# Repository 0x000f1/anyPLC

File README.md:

<div align="center">

# anyPLC

**Compact 50 × 50 mm, 4-Layer ESP32-C3 Industrial PWM & Telemetry Controller for ESPHome**

<br>

*Raytraced 3D render of the **anyPLC Rev 1.1** front side (50 × 50 mm, 4-layer PCB)*

</div>

---

## Overview

**anyPLC** is a compact, industrial-grade, Wi-Fi/BLE smart controller built around the **ESP32-C3-MINI-1** module and designed for seamless integration with **ESPHome** and **Home Assistant**.

It is engineered for reliable, closed-loop control of **12–24 V DC loads** in tight enclosures, including:
* High-power 12 V / 24 V PWM cooling fans with real-time RPM (tachometer) feedback
* DC water/dosing pumps, solenoids, valves, and inductive actuators (protected by onboard freewheeling diodes)
* High-current DC LED strips or low-voltage resistive heaters
* Autonomous monitoring setups requiring real-time bus voltage/current telemetry and hardware watchdog recovery

<details>
<summary><b>View Front & Back PCB Renders</b></summary>
<br>

| Front Side (`F.Cu`) | Back Side (`B.Cu`) |
| :---: | :---: |
|  |  |

</details>

---

## Hardware Architecture & Specifications

| Subsystem | Components & Specifications |
| :--- | :--- |
| **MCU & Radio** | **ESP32-C3-MINI-1** (`U4`) — 32-bit RISC-V, Wi-Fi 4 + BLE 5, integrated 40 MHz crystal & flash, unobstructed edge antenna keepout |
| **Power Input** | **12–24 V DC** (`J1`), **8 A** input fuse (`F1`), P-channel MOSFET reverse-polarity protection (`Q1`) with ~15 V V<sub>GS</sub> Zener clamp (`DZ1`, `R2`), and **SMBJ26A** TVS surge suppressor (`D1`) |
| **Power Rails** | Dual independent buck stages:<br>• **+5 V Rail (`U2`):** `TPS54360B` (~4.98 V, ~485 kHz, `B560C` catch diode `D_BUCK1`, `L1`)<br>• **+3.3 V Rail (`U3`):** `SY8089` (~3.33 V, fed from +5 V, `L2`) |
| **Power Telemetry** | **INA226** (`U1`) bus voltage & current monitor across a **10 mΩ (2512)** shunt (`R1`) with Kelvin sensing (`R3`/`R4` 10 Ω + `C3`), I2C address **`0x44`**, open-drain `INA_ALERT` pull-up (`R_INA1` 10 kΩ) |
| **Dual PWM Outputs** | 2× low-side N-channel PWM MOSFET stages (`Q2`, `Q3`) driven at +5 V by a dedicated dual gate driver (`U_DRV1`, 10 Ω gate resistors `R13`/`R18`, 10 kΩ pulldowns `R14`/`R19`), **B560C** (60 V / 5 A) freewheeling diodes (`D3`, `D5`), and per-channel active LEDs (`D4`, `D6`) |
| **Tachometer Inputs** | 2× optocoupled open-collector/open-drain tachometer inputs (`U7`, `U8` — `TLP293`), reverse-blocking diodes (`D_TCH1`/`D_TCH2` `1N4148W`), ~1.3 mA LED drive from +5 V, 10 kΩ output pull-ups (`R15`/`R20`) to +3.3 V |
| **Expansion Ports** | Dedicated **I2C** (`J2`, onboard 4.7 kΩ pull-ups `R9`/`R10`) and **UART** (`J3`, 100 Ω series resistors `R11`/`R12`), protected by **SRV05-4** ESD diode array (`U6`) |
| **Hardware Watchdog** | External **STWD100** watchdog timer (`U5`) tied to MCU `EN`, with hardware enable/disable solder jumper (`JP1`, 4.7 kΩ pull-up `R_WD_EN1`) |
| **Status & Debug** | Addressable RGB status LED (`D_RGB1`, WS2812-type) and 2×4 pogo-pad programming/debug interface (`J6`) exposing UART, native USB, `EN`, and `BOOT` |
| **PCB Form Factor** | **50 × 50 mm**, 4-layer stackup (`F.Cu` / `GND` / `Power` / `B.Cu`), 1.6 mm FR-4, teardrops, and dual-sided fiducials for automated PCBA |

---

## Connector Pinouts

### `J1` — Power Input (12–24 V DC)
| Pin | Net | Function |
| :---: | :--- | :--- |
| 1 | `VIN+` | 12–24 V DC input (via `F1` 8 A fuse & `Q1` reverse-polarity MOSFET) |
| 2 | `GND` | System ground |

### `J4` (CH1) & `J5` (CH2) — PWM Output & Tachometer Terminals
| Pin | Net | Function |
| :---: | :--- | :--- |
| 1 | `+V_IN_MAIN` | Protected supply positive (12–24 V DC, load `+`) |
| 2 | `PWM OUT` | Low-side MOSFET Drain (load `-`, flyback diode to Pin 1) |
| 3 | `GND` | System ground |
| 4 | `+5V` | Regulated +5 V auxiliary supply (e.g., for fan electronics / sensors) |
| 5 | `TACHO` | Optocoupled tachometer input (active-low open-collector/open-drain pull-down) |

### `J2` (I2C) & `J3` (UART) — Expansion Ports (**3.3 V Logic Only**)
| Pin | `J2` (I2C) | `J3` (UART) |
| :---: | :--- | :--- |
| 1 | `GND` | `GND` |
| 2 | `+3.3V` | `+3.3V` |
| 3 | `I2C_SDA` (4.7 kΩ pull-up to 3.3 V) | `UART_TX` (via 100 Ω `R11`, ESD protected) |
| 4 | `I2C_SCL` (4.7 kΩ pull-up to 3.3 V) | `UART_RX` (via 100 Ω `R12`, ESD protected) |

### `J6` — Programming & Debug Pogo-Pad (2×4, Bottom Side)
| Pin | Function | Pin | Function |
| :---: | :--- | :---: | :--- |
| 1 | `+3.3V` | 5 | `EN` (Reset) |
| 2 | `GND` | 6 | `BOOT` (`GPIO9`) |
| 3 | `UART_TX` (ESP TXD) | 7 | `USB_D+` |
| 4 | `UART_RX` (ESP RXD) | 8 | `USB_D-` |

### `JP1` — Watchdog Enable Jumper (Bottom Side)
| State | Watchdog (`STWD100`) Behavior |
| :--- | :--- |
| **OPEN** *(default)* | **Disabled** (`R_WD_EN1` pulls enable high). Required during firmware flashing and bench debugging. |
| **CLOSED** *(bridged)* | **Enabled**. Firmware must periodically toggle `WDI` to prevent automatic MCU resets. |

---

## Important Notes, Precautions & Known Limitations

Read these before assembly, flashing, or field deployment:

1. **Keep `JP1` OPEN when flashing:** With `JP1` bridged, the external `STWD100` watchdog receives no `WDI` pulses while the ESP32-C3 is in ROM bootloader mode and will continuously reset the chip. Bridge `JP1` only after flashing firmware that actively feeds `WDI`.
2. **Disconnect `J3` during UART flashing:** `J6` (pogo-pad) and `J3` (UART expansion port) share the same `UART_TX` / `UART_RX` lines (coupled through 100 Ω `R11`/`R12`). Unplug any peripheral on `J3` while flashing through `J6` to avoid bus contention.
3. **`J2` and `J3` are strictly 3.3 V logic:** The `SRV05-4` ESD array (`U6`) clamps I/O pins directly to `+3.3V`. Connecting 5 V I2C or UART logic will forward-bias the clamp diodes above ~4 V and back-feed the 3.3 V rail and ESP32-C3 pins.
4. **INA226 I2C address is `0x44` (not `0x40`):** `U1` has `A1` strapped to `+3.3V` and `A0` to `GND`. Configure `address: 0x44` in ESPHome. Note that `0x44` is also the default I2C address of **SHT3x** temperature/humidity sensors — if connecting an SHT3x to `J2`, strap the sensor's address pin to `0x45` to avoid a bus collision.
5. **No per-port PTC fuses on auxiliary rails:** `+3.3V` (`J2.2`, `J3.2`) and `+5V` (`J4.4`, `J5.4`) connect directly to the internal buck rails. Shorting an external sensor cable will brown out the MCU (`+3.3V`) or put `U2` (`+5V` TPS54360B) into hiccup mode, collapsing both rails.
6. **No external ESD diodes on `J6` USB lines:** `USB_D+` and `USB_D-` run directly from `J6` to `U4`. The pogo-pad header is intended for ESD-safe bench/factory programming rather than exposed field hot-plugging.
7. **24 V hot-plug transient margin:** `SMBJ26A` (`D1`) has a peak clamping voltage up to 42.1 V under rated surge current, while the `INA226` absolute maximum rating is 40 V. Operate within 12–24 V DC nominal and avoid severe unbuffered inductive hot-plug spikes.
8. **First-board bring-up verification:** On initial power-up at 24 V, verify the `+5V` (~4.98 V) and `+3.3V` (~3.33 V) rails before soldering `JP1`, and scope-check the `U2` switch node (`SW`) under load to confirm overshoot stays safely within the `B560C` 60 V rating.

---

## Bring-Up & Flashing Quick Checklist

1. Inspect the assembled board for solder bridges, confirm `JP1` is **open**, and ensure nothing is connected to `J3`.
2. Power the board from a current-limited bench supply (12–24 V DC, ~150 mA limit initially) and verify `+5V` and `+3.3V` rails.
3. Connect your USB/UART programmer to `J6` and flash your ESPHome firmware (include `address: 0x44` in the `ina226:` block).
4. Verify I2C bus discovery (`0x44` for INA226), PWM channel switching (`D4`/`D6`), and tachometer pulse counting.
5. Once your firmware reliably toggles the `WDI` pin, bridge `JP1` to activate the hardware watchdog for deployment.

---

## PCB Manufacturing & DFM

* **Dimensions:** 50.0 × 50.0 mm
* **Layers:** 4 layers (`F.Cu` Signal / `In1.Cu` Solid GND / `In2.Cu` Split Power `+V_IN_MAIN`, `+5V`, `+3.3V` / `B.Cu` Signal)
* **Design Rules:** Verified against JLCPCB 4-layer standard capabilities (min clearance 0.125 mm, min track 0.15 mm, standard vias 0.50 mm / 0.30 mm drill, `U2` thermal pad vias 0.20 mm drill)
* **DFM Features:** Teardrops enabled on pads and vias, 3+3 asymmetric fiducial markers (`F.Cu` and `B.Cu`), tented vias, `JLCJLCJLCJLC` order-number placeholder on `B.Silkscreen`
* **Assembly Note:** If hand-soldering with paste and hot air, request tented/plugged vias or watch solder wicking on the `U2` thermal vias and the central hole of `U4` pad 49.

---

## Repository Structure

```text
anyPLC/
├── anyPLC.kicad_pro          # KiCad 10 project file
├── anyPLC.kicad_sch          # Multi-sheet schematic
├── anyPLC.kicad_pcb          # 4-layer PCB layout
├── docs/
│   └── images/               # Raytraced 3D renders & documentation assets
├── production/               # Gerber, Drill, BOM, CPL, and iBOM outputs
└── README.md
```

---

## Hardware Revisions

* **Rev 1.1** *(Current)* — Initial 4-layer production candidate (`DRC: 0 errors, 0 unconnected`, netlist-audited). Includes teardrops, dual-sided fiducials, repository QR code, ESD markings, and full bottom-side pinout silkscreen.

---

## License

* **Hardware** (schematics, PCB layout, manufacturing files): Licensed under the **CERN Open Hardware Licence Version 2 - Strongly Reciprocal (CERN-OHL-S v2)**.
* **Software & Documentation** (ESPHome configs, scripts, docs): Licensed under the **MIT License**.

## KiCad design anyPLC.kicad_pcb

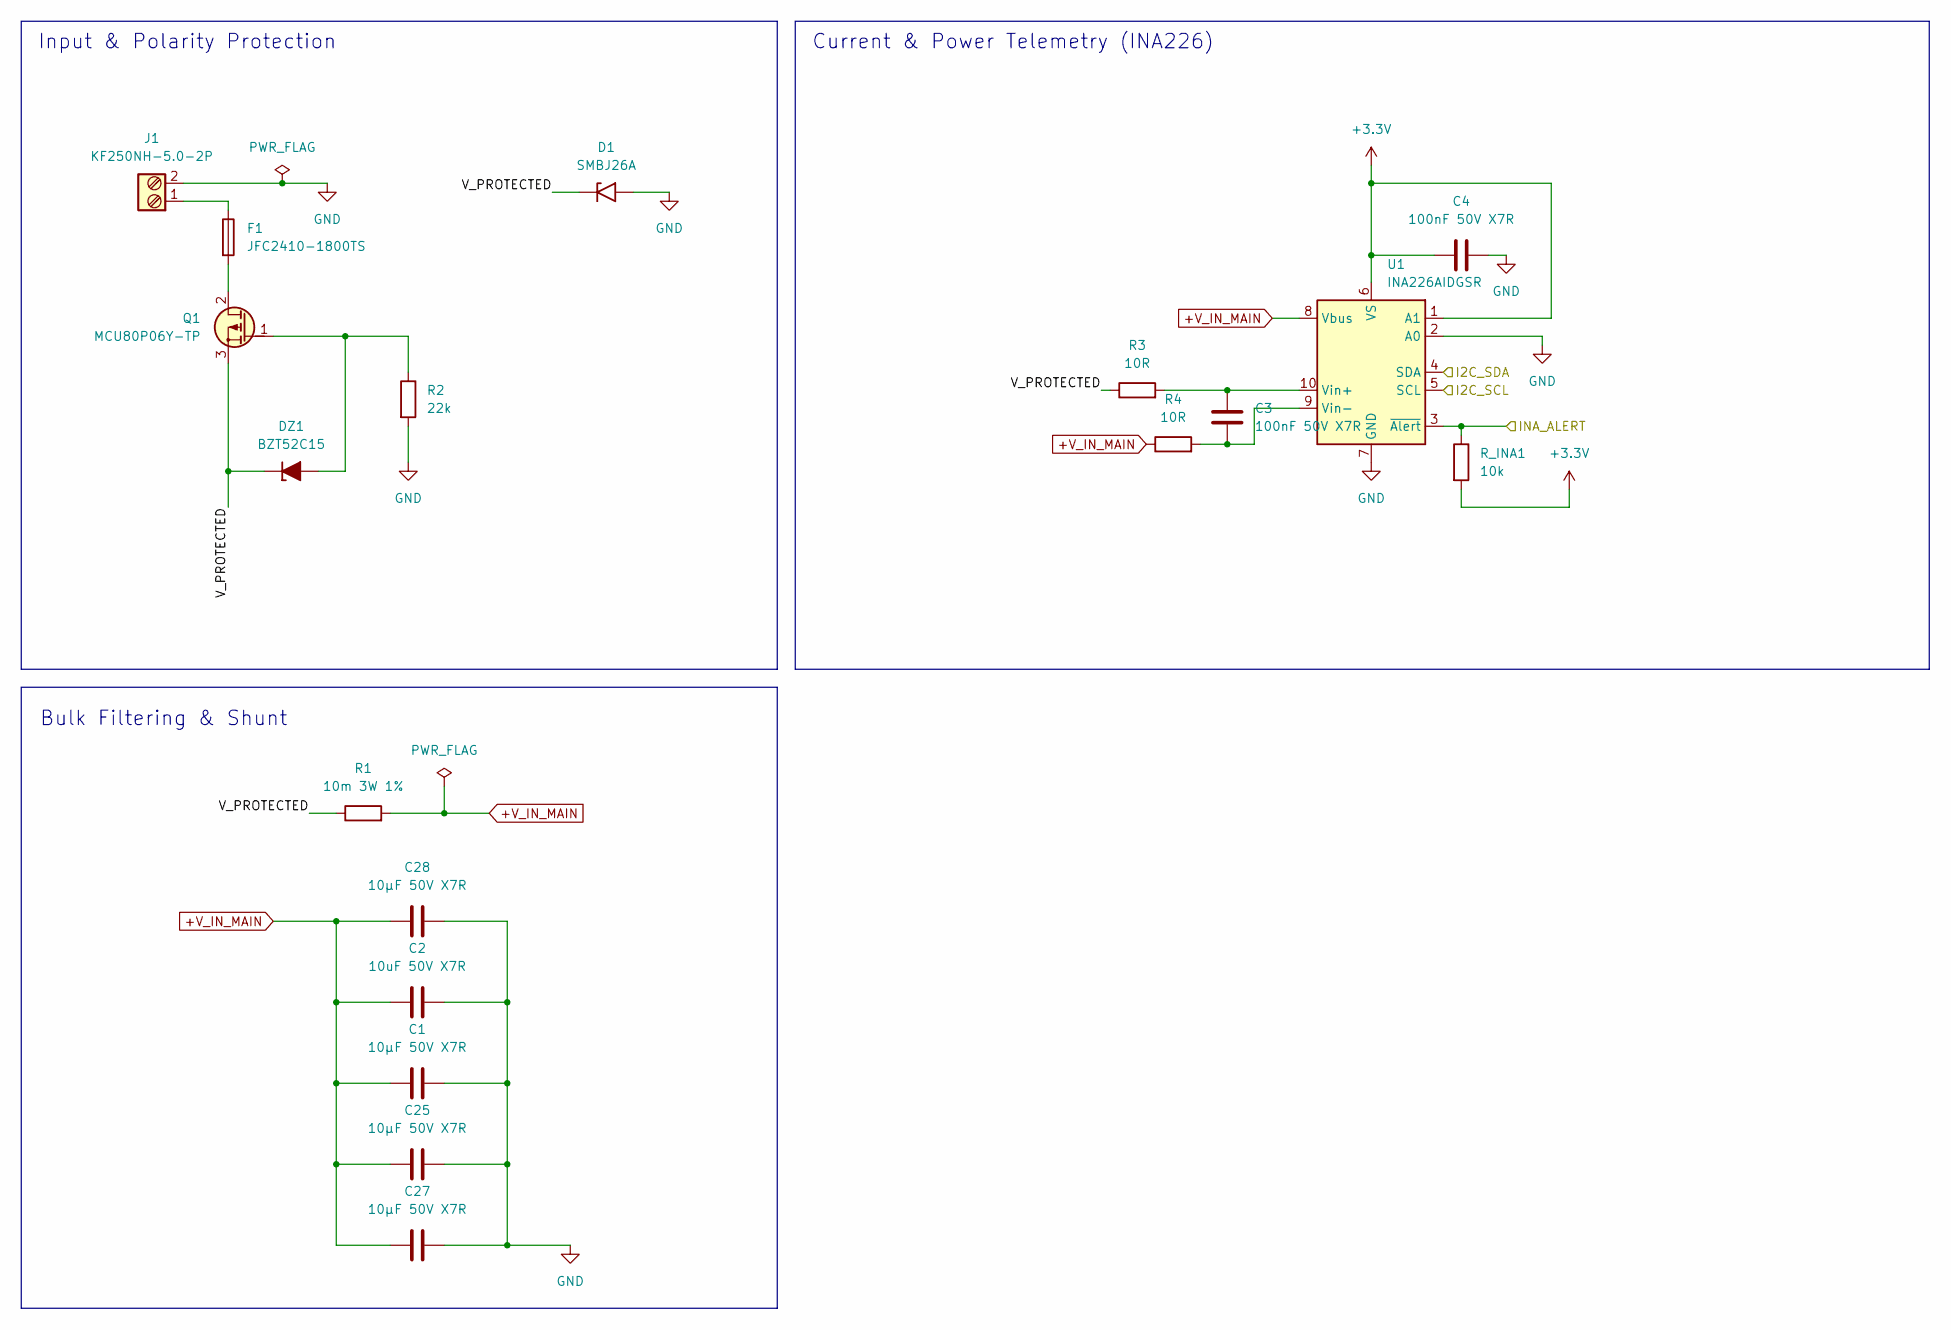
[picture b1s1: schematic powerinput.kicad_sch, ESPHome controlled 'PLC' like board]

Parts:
C1, C25, C27, C28: 10µF 50V X7R; C_1206_3216Metric_Pad1.33x1.80mm_HandSolder
C2: 10uF 50V X7R; C_1206_3216Metric_Pad1.33x1.80mm_HandSolder
C3, C4: 100nF 50V X7R; C_0603_1608Metric_Pad1.08x0.95mm_HandSolder
D1: SMBJ26A; D_SMB_Handsoldering
DZ1: BZT52C15; D_SOD-123
F1: JFC2410-1800TS; F2410
J1: KF250NH-5.0-2P; CONN-TH_KF250NH-5.0-2P
Q1: MCU80P06Y-TP; TO-252-2
R1: 10m 3W 1%; R_2512_6332Metric_Pad1.40x3.35mm_HandSolder
R2: 22k; R_0603_1608Metric_Pad0.98x0.95mm_HandSolder
R3, R4: 10R; R_0603_1608Metric_Pad0.98x0.95mm_HandSolder
R_INA1: 10k; R_0603_1608Metric_Pad0.98x0.95mm_HandSolder
U1: INA226AIDGSR; TSSOP-10_3x3mm_P0.5mm

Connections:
+3.3V: C4.1, R_INA1.2, U1.1 (A1), U1.6 (VS); also elsewhere on the board
+V_IN_MAIN: C1.1, C2.2, C25.1, C27.1, C28.1, R1.2, R4.1, U1.8 (Vbus); also elsewhere on the board
/MCU Core/I2C_SCL: U1.5 (SCL); also elsewhere on the board
/MCU Core/I2C_SDA: U1.4 (SDA); also elsewhere on the board
/MCU Core/INA_ALERT: R_INA1.1, U1.3 (~Alert); also elsewhere on the board
/Power Input/V_PROTECTED: D1.1 (A1), DZ1.1 (K), Q1.3 (S), R1.1, R3.1
GND: C1.2, C2.1, C4.2, C25.2, C27.2, C28.2, D1.2 (A2), J1.2, R2.2, U1.2 (A0), U1.7 (GND); also elsewhere on the board
unnamed: DZ1.2 (A), Q1.1 (G), R2.1
unnamed: F1.1, J1.1
unnamed: F1.2, Q1.2 (D)
unnamed: C3.1, R3.2, U1.10 (Vin+)
unnamed: C3.2, R4.2, U1.9 (Vin-)

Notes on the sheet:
Input & Polarity Protection
Bulk Filtering & Shunt
Current & Power Telemetry (INA226)

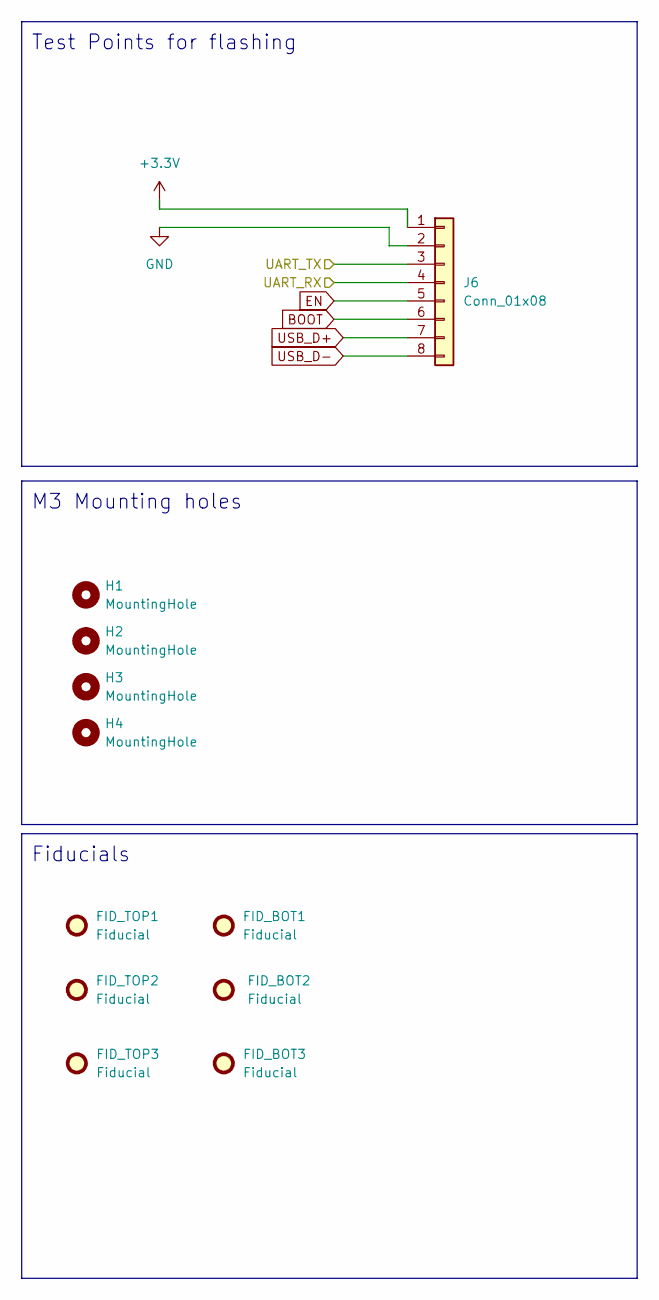
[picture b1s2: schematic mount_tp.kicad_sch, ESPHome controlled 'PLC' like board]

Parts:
FID_BOT1, FID_BOT2, FID_BOT3: Fiducial; Fiducial_1mm_Mask2mm
FID_TOP1, FID_TOP2, FID_TOP3: Fiducial; Fiducial_1mm_Mask2mm
H1, H2, H3, H4: MountingHole; MountingHole_3.2mm_M3_ISO14580
J6: Conn_01x08; TestPoint_2x04_P2.54mm_D1.6mm_SMD

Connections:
+3.3V: J6.1; also elsewhere on the board
/MCU Core/UART_RX: J6.4; also elsewhere on the board
/MCU Core/UART_TX: J6.3; also elsewhere on the board
BOOT: J6.6; also elsewhere on the board
EN: J6.5; also elsewhere on the board
GND: J6.2; also elsewhere on the board
USB_D+: J6.7; also elsewhere on the board
USB_D-: J6.8; also elsewhere on the board

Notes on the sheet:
M3 Mounting holes
Test Points for flashing
Fiducials

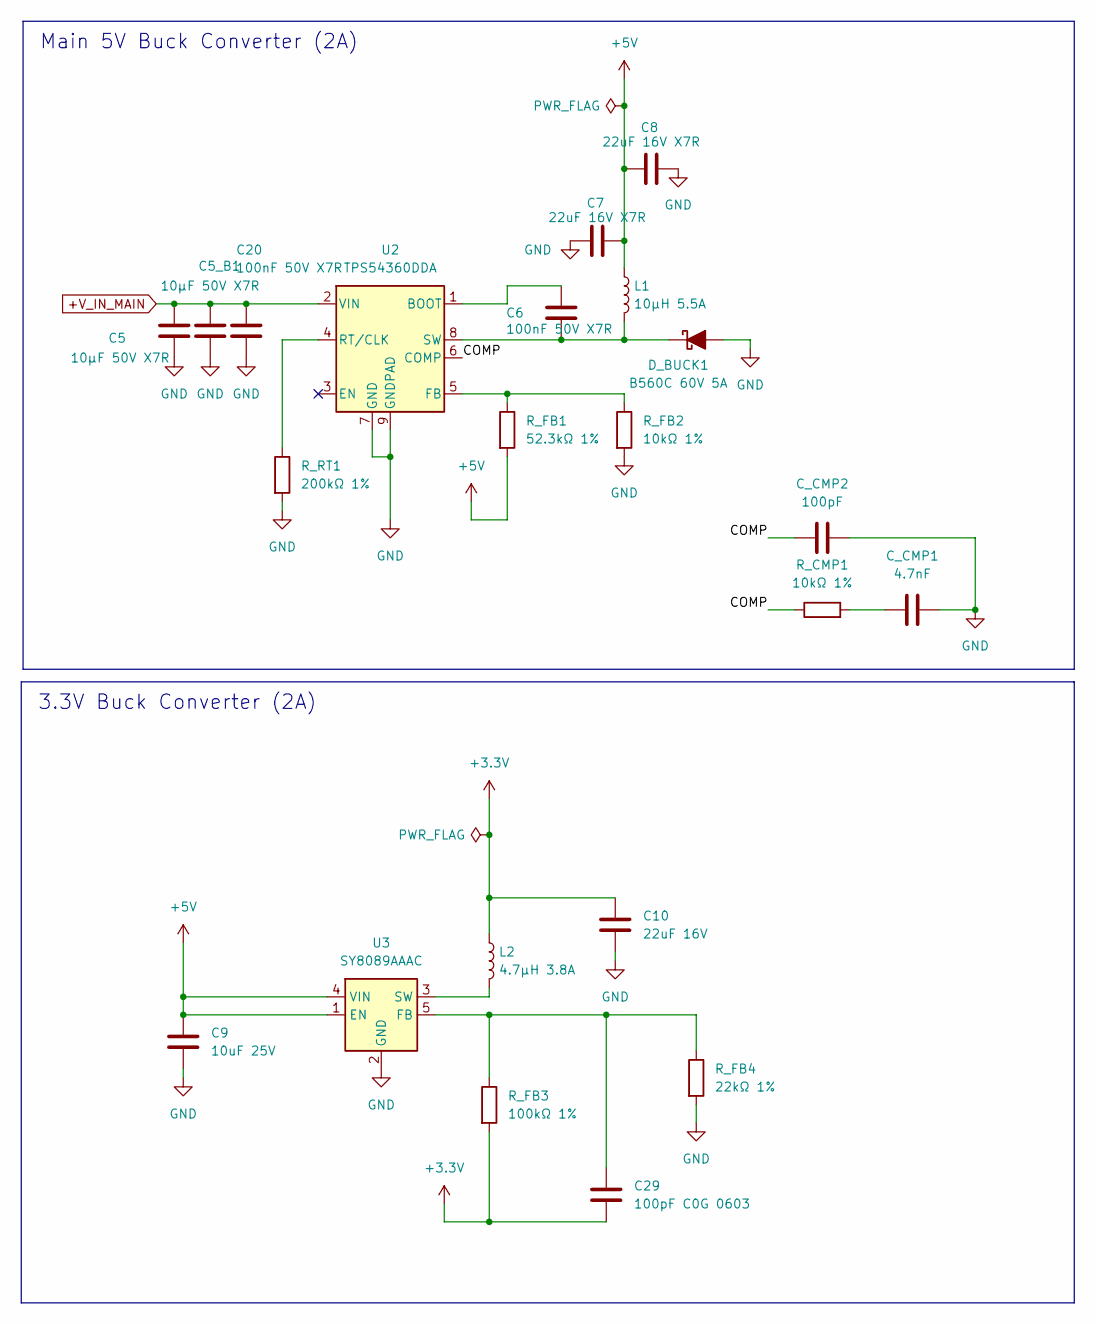
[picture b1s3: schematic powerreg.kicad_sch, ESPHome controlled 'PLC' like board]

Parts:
C5, C5_B1: 10µF 50V X7R; C_1206_3216Metric_Pad1.33x1.80mm_HandSolder
C6, C20: 100nF 50V X7R; C_0603_1608Metric_Pad1.08x0.95mm_HandSolder
C7, C8: 22uF 16V X7R; C_1206_3216Metric_Pad1.33x1.80mm_HandSolder
C9: 10uF 25V; C_0805_2012Metric_Pad1.18x1.45mm_HandSolder
C10: 22uF 16V; C_1206_3216Metric_Pad1.33x1.80mm_HandSolder
C29: 100pF C0G 0603; C_0603_1608Metric_Pad1.08x0.95mm_HandSolder
C_CMP1: 4.7nF; C_0603_1608Metric_Pad1.08x0.95mm_HandSolder
C_CMP2: 100pF; C_0603_1608Metric_Pad1.08x0.95mm_HandSolder
D_BUCK1: B560C 60V 5A; D_SMC_Handsoldering
L1: 10µH 5.5A; IND-SMD_L7.3-W6.6
L2: 4.7µH 3.8A; IND-SMD_L5.0-W5.0_FNR50XXS
R_CMP1: 10kΩ 1%; R_0603_1608Metric_Pad0.98x0.95mm_HandSolder
R_FB1: 52.3kΩ 1%; R_0603_1608Metric_Pad0.98x0.95mm_HandSolder
R_FB2: 10kΩ 1%; R_0603_1608Metric_Pad0.98x0.95mm_HandSolder
R_FB3: 100kΩ 1%; R_0603_1608Metric_Pad0.98x0.95mm_HandSolder
R_FB4: 22kΩ 1%; R_0603_1608Metric_Pad0.98x0.95mm_HandSolder
R_RT1: 200kΩ 1%; R_0603_1608Metric_Pad0.98x0.95mm_HandSolder
U2: TPS54360DDA; SOIC-8-1EP_3.9x4.9mm_P1.27mm_EP2.41x3.3mm
U3: SY8089AAAC; SOT-23-5_HandSoldering

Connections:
+3.3V: C10.1, C29.2, L2.1, R_FB3.2; also elsewhere on the board
+5V: C7.1, C8.1, C9.1, L1.1, R_FB1.2, U3.1 (EN), U3.4 (VIN); also elsewhere on the board
+V_IN_MAIN: C5.2, C5_B1.2, C20.2, U2.2 (VIN); also elsewhere on the board
/Power Regulators/COMP: C_CMP2.1, R_CMP1.1, U2.6 (COMP)
GND: C5.1, C5_B1.1, C7.2, C8.2, C9.2, C10.2, C20.1, C_CMP1.2, C_CMP2.2, D_BUCK1.2 (A), R_FB2.2, R_FB4.2, R_RT1.2, U2.7 (GND), U2.9 (GNDPAD), U3.2 (GND); also elsewhere on the board
unnamed: C_CMP1.1, R_CMP1.2
unnamed: C6.1, D_BUCK1.1 (K), L1.2, U2.8 (SW)
unnamed: C6.2, U2.1 (BOOT)
unnamed: R_FB1.1, R_FB2.1, U2.5 (FB)
unnamed: R_RT1.1, U2.4 (RT/CLK)
unnamed: C29.1, R_FB3.1, R_FB4.1, U3.5 (FB)
unnamed: L2.2, U3.3 (SW)

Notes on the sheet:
Main 5V Buck Converter (2A)
3.3V Buck Converter (2A)

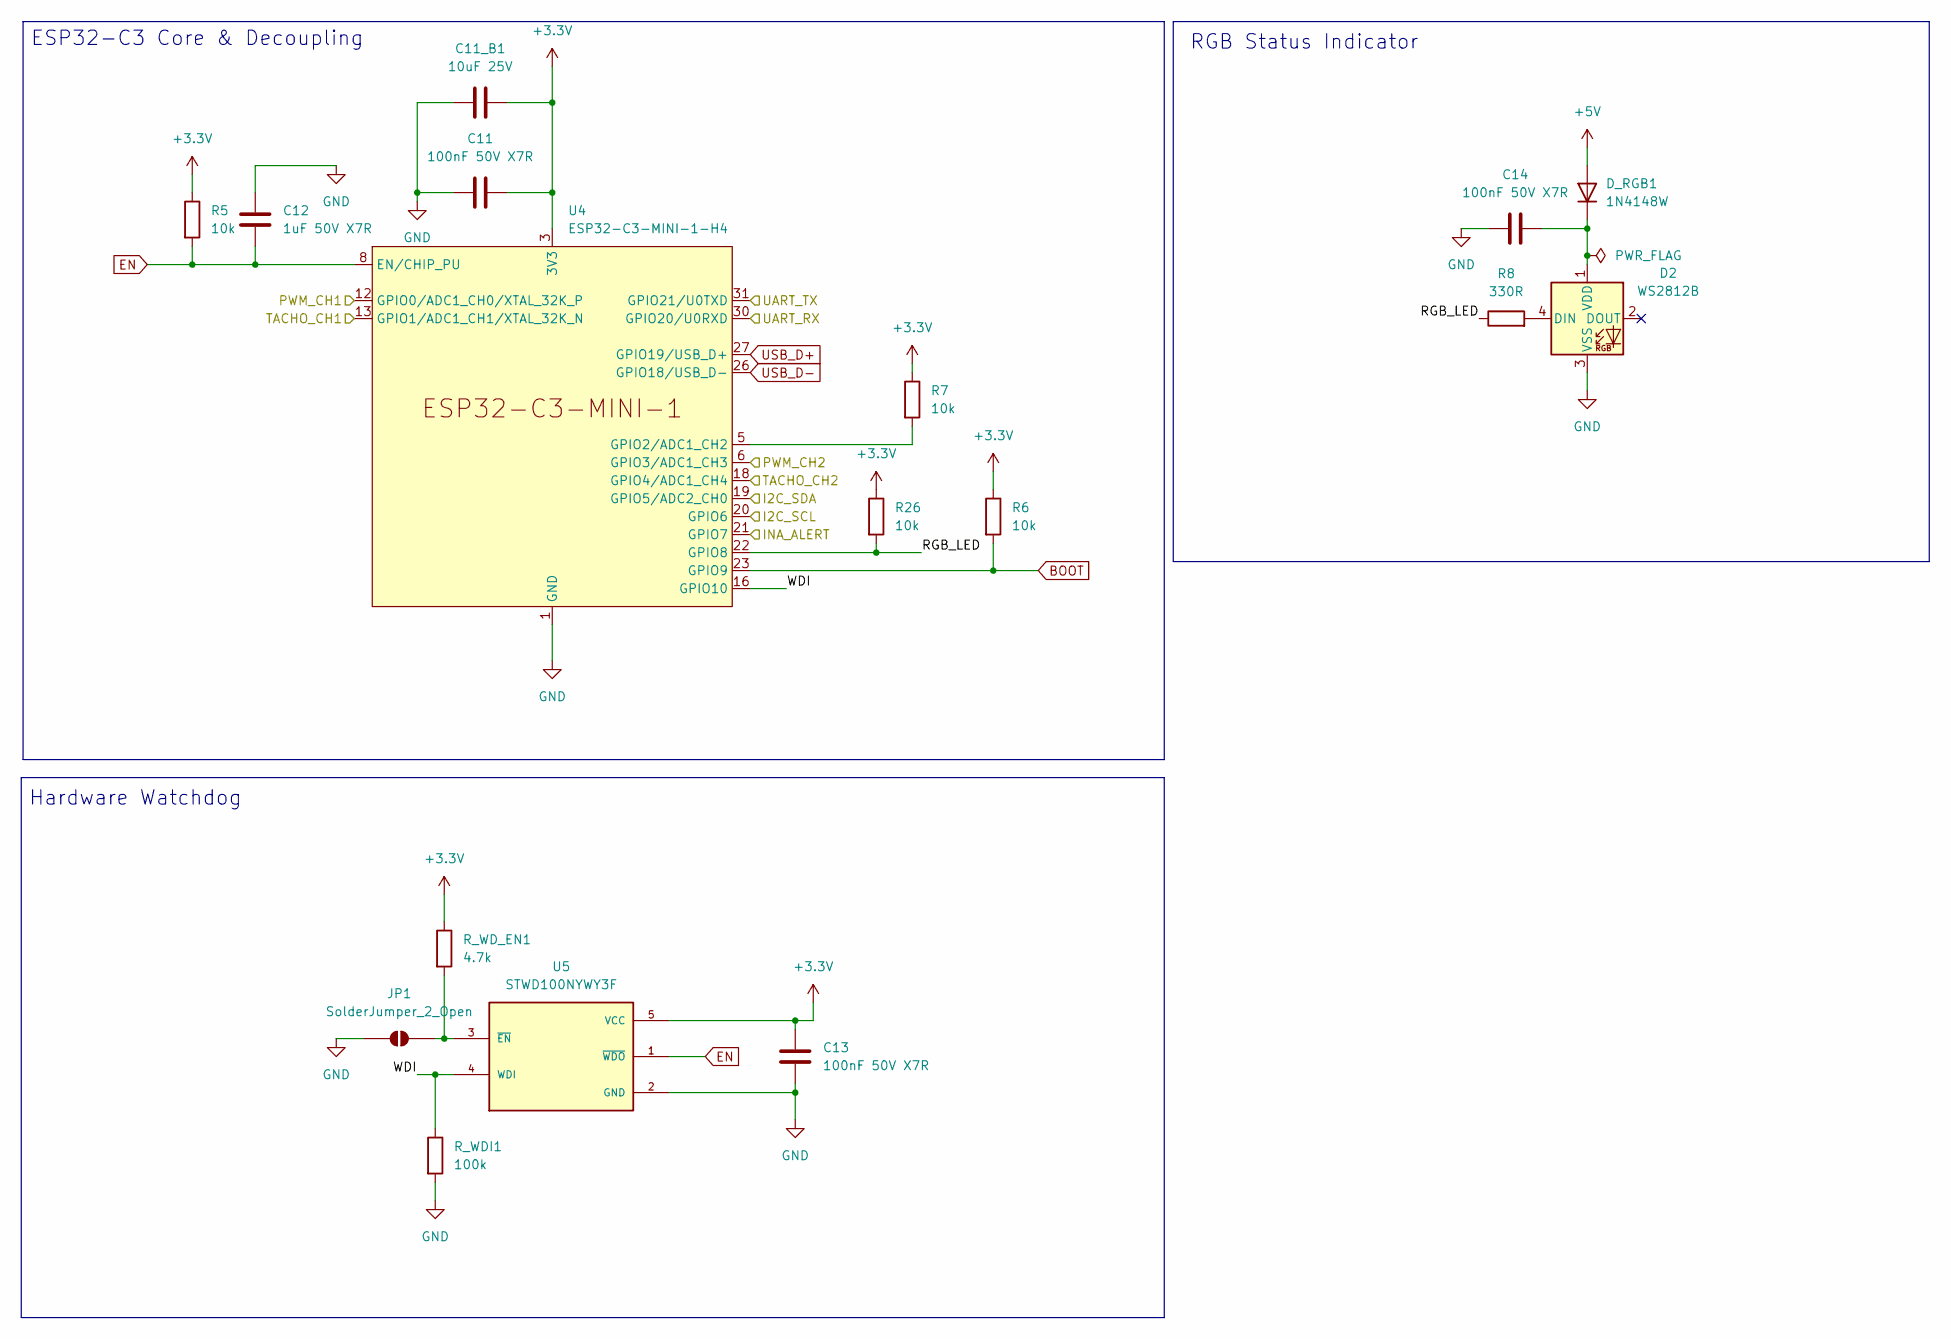
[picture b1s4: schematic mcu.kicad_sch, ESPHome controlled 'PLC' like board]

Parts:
C11, C13, C14: 100nF 50V X7R; C_0603_1608Metric_Pad1.08x0.95mm_HandSolder
C11_B1: 10uF 25V; C_0805_2012Metric_Pad1.18x1.45mm_HandSolder
C12: 1uF 50V X7R; C_0603_1608Metric_Pad1.08x0.95mm_HandSolder
D2: WS2812B; LED_WS2812B_PLCC4_5.0x5.0mm_P3.2mm
D_RGB1: 1N4148W; D_SOD-123
JP1: SolderJumper_2_Open; SolderJumper-2_P1.3mm_Open_RoundedPad1.0x1.5mm
R5, R6, R7, R26: 10k; R_0603_1608Metric_Pad0.98x0.95mm_HandSolder
R8: 330R; R_0603_1608Metric_Pad0.98x0.95mm_HandSolder
R_WDI1: 100k; R_0603_1608Metric_Pad0.98x0.95mm_HandSolder
R_WD_EN1: 4.7k; R_0603_1608Metric_Pad0.98x0.95mm_HandSolder
U4: ESP32-C3-MINI-1-H4; ESP32-C3-MINI-1
U5: STWD100NYWY3F; SOT-23-5_HandSoldering; MPN STWD100NYWY3F

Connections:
+3.3V: C11.2, C11_B1.2, C13.1, R5.1, R6.1, R7.1, R26.1, R_WD_EN1.1, U4.3 (3V3), U5.5 (VCC); also elsewhere on the board
+5V: D_RGB1.2 (A); also elsewhere on the board
/MCU Core/I2C_SCL: U4.20 (GPIO6); also elsewhere on the board
/MCU Core/I2C_SDA: U4.19 (GPIO5/ADC2_CH0); also elsewhere on the board
/MCU Core/INA_ALERT: U4.21 (GPIO7); also elsewhere on the board
/MCU Core/PWM_CH1: U4.12 (GPIO0/ADC1_CH0/XTAL_32K_P); also elsewhere on the board
/MCU Core/PWM_CH2: U4.6 (GPIO3/ADC1_CH3); also elsewhere on the board
/MCU Core/RGB_LED: R8.1, R26.2, U4.22 (GPIO8)
/MCU Core/TACHO_CH1: U4.13 (GPIO1/ADC1_CH1/XTAL_32K_N); also elsewhere on the board
/MCU Core/TACHO_CH2: U4.18 (GPIO4/ADC1_CH4); also elsewhere on the board
/MCU Core/UART_RX: U4.30 (GPIO20/U0RXD); also elsewhere on the board
/MCU Core/UART_TX: U4.31 (GPIO21/U0TXD); also elsewhere on the board
/MCU Core/WDI: R_WDI1.1, U4.16 (GPIO10), U5.4 (WDI)
BOOT: R6.2, U4.23 (GPIO9); also elsewhere on the board
EN: C12.2, R5.2, U4.8 (EN/CHIP_PU), U5.1 (~WDO); also elsewhere on the board
GND: C11.1, C11_B1.1, C12.1, C13.2, C14.1, D2.3 (VSS), JP1.1 (A), R_WDI1.2, U4.1 (GND), U4.2 (GND), U4.11 (GND), U4.14 (GND), U4.36 (GND), U4.37 (GND), U4.38 (GND), U4.39 (GND), U4.40 (GND), U4.41 (GND), U4.42 (GND), U4.43 (GND), U4.44 (GND), U4.45 (GND), U4.46 (GND), U4.47 (GND), U4.48 (GND), U4.49 (GND), U4.50 (GND), U4.51 (GND), U4.52 (GND), U4.53 (GND), U5.2 (GND); also elsewhere on the board
unnamed: D2.4 (DIN), R8.2
unnamed: C14.2, D2.1 (VDD), D_RGB1.1 (K)
unnamed: JP1.2 (B), R_WD_EN1.2, U5.3 (~EN)
unnamed: R7.2, U4.5 (GPIO2/ADC1_CH2)
USB_D+: U4.27 (GPIO19/USB_D+); also elsewhere on the board
USB_D-: U4.26 (GPIO18/USB_D-); also elsewhere on the board

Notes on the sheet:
Hardware Watchdog
RGB Status Indicator
ESP32-C3 Core & Decoupling

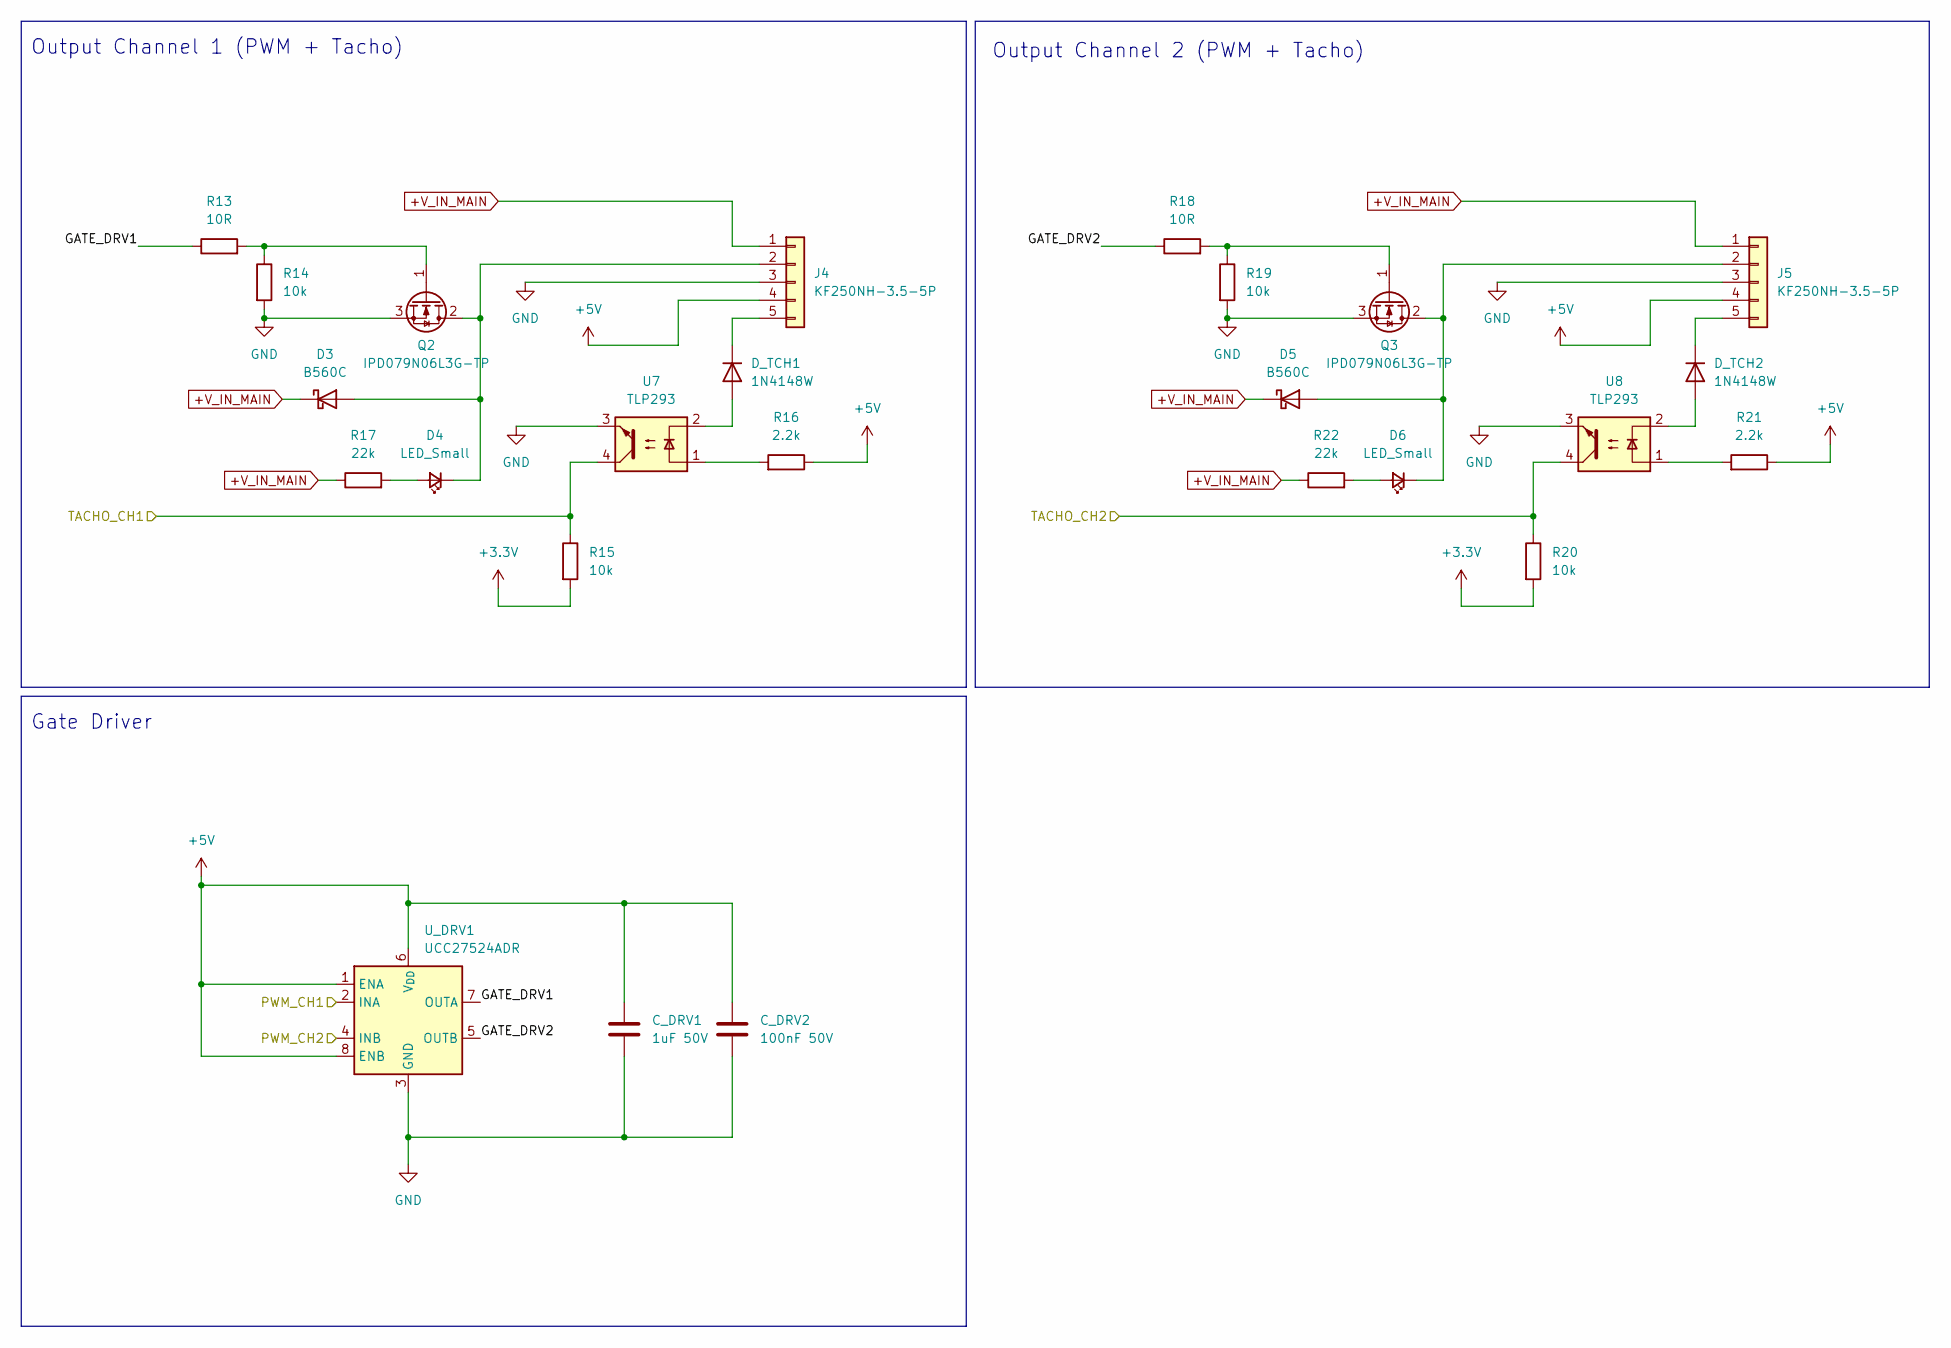
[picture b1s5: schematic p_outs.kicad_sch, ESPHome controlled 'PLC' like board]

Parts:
C_DRV1: 1uF 50V; C_0603_1608Metric_Pad1.08x0.95mm_HandSolder
C_DRV2: 100nF 50V; C_0603_1608Metric_Pad1.08x0.95mm_HandSolder
D3, D5: B560C; D_SMC_Handsoldering
D4, D6: LED_Small; LED_0603_1608Metric_Pad1.05x0.95mm_HandSolder
D_TCH1, D_TCH2: 1N4148W; D_SOD-123
J4, J5: KF250NH-3.5-5P; CONN-TH_KF250NH-3.5-5P
Q2, Q3: IPD079N06L3G-TP; TO-252-2
R13, R18: 10R; R_0603_1608Metric_Pad0.98x0.95mm_HandSolder
R14, R15, R19, R20: 10k; R_0603_1608Metric_Pad0.98x0.95mm_HandSolder
R16, R21: 2.2k; R_0603_1608Metric_Pad0.98x0.95mm_HandSolder
R17, R22: 22k; R_0603_1608Metric_Pad0.98x0.95mm_HandSolder
U7, U8: TLP293; SOP-4_4.4x2.6mm_P1.27mm
U_DRV1: UCC27524ADR; SOIC-8_3.9x4.9mm_P1.27mm

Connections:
+3.3V: R15.2, R20.2; also elsewhere on the board
+5V: C_DRV1.1, C_DRV2.1, J4.4, J5.4, R16.1, R21.1, U_DRV1.1 (ENA), U_DRV1.6 (V_{DD}), U_DRV1.8 (ENB); also elsewhere on the board
+V_IN_MAIN: D3.1 (K), D5.1 (K), J4.1, J5.1, R17.1, R22.1; also elsewhere on the board
/MCU Core/PWM_CH1: U_DRV1.2 (INA); also elsewhere on the board
/MCU Core/PWM_CH2: U_DRV1.4 (INB); also elsewhere on the board
/MCU Core/TACHO_CH1: R15.1, U7.4; also elsewhere on the board
/MCU Core/TACHO_CH2: R20.1, U8.4; also elsewhere on the board
/Power Outputs/GATE_DRV1: R13.1, U_DRV1.7 (OUTA)
/Power Outputs/GATE_DRV2: R18.1, U_DRV1.5 (OUTB)
GND: C_DRV1.2, C_DRV2.2, J4.3, J5.3, Q2.3 (S), Q3.3 (S), R14.2, R19.2, U7.3, U8.3, U_DRV1.3 (GND); also elsewhere on the board
unnamed: D3.2 (A), D4.1 (K), J4.2, Q2.2 (D)
unnamed: D4.2 (A), R17.2
unnamed: D5.2 (A), D6.1 (K), J5.2, Q3.2 (D)
unnamed: D6.2 (A), R22.2
unnamed: D_TCH1.2 (A), U7.2
unnamed: D_TCH1.1 (K), J4.5
unnamed: D_TCH2.2 (A), U8.2
unnamed: D_TCH2.1 (K), J5.5
unnamed: Q2.1 (G), R13.2, R14.1
unnamed: Q3.1 (G), R18.2, R19.1
unnamed: R16.2, U7.1
unnamed: R21.2, U8.1

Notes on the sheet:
Gate Driver
Output Channel 1 (PWM + Tacho)
Output Channel 2 (PWM + Tacho)

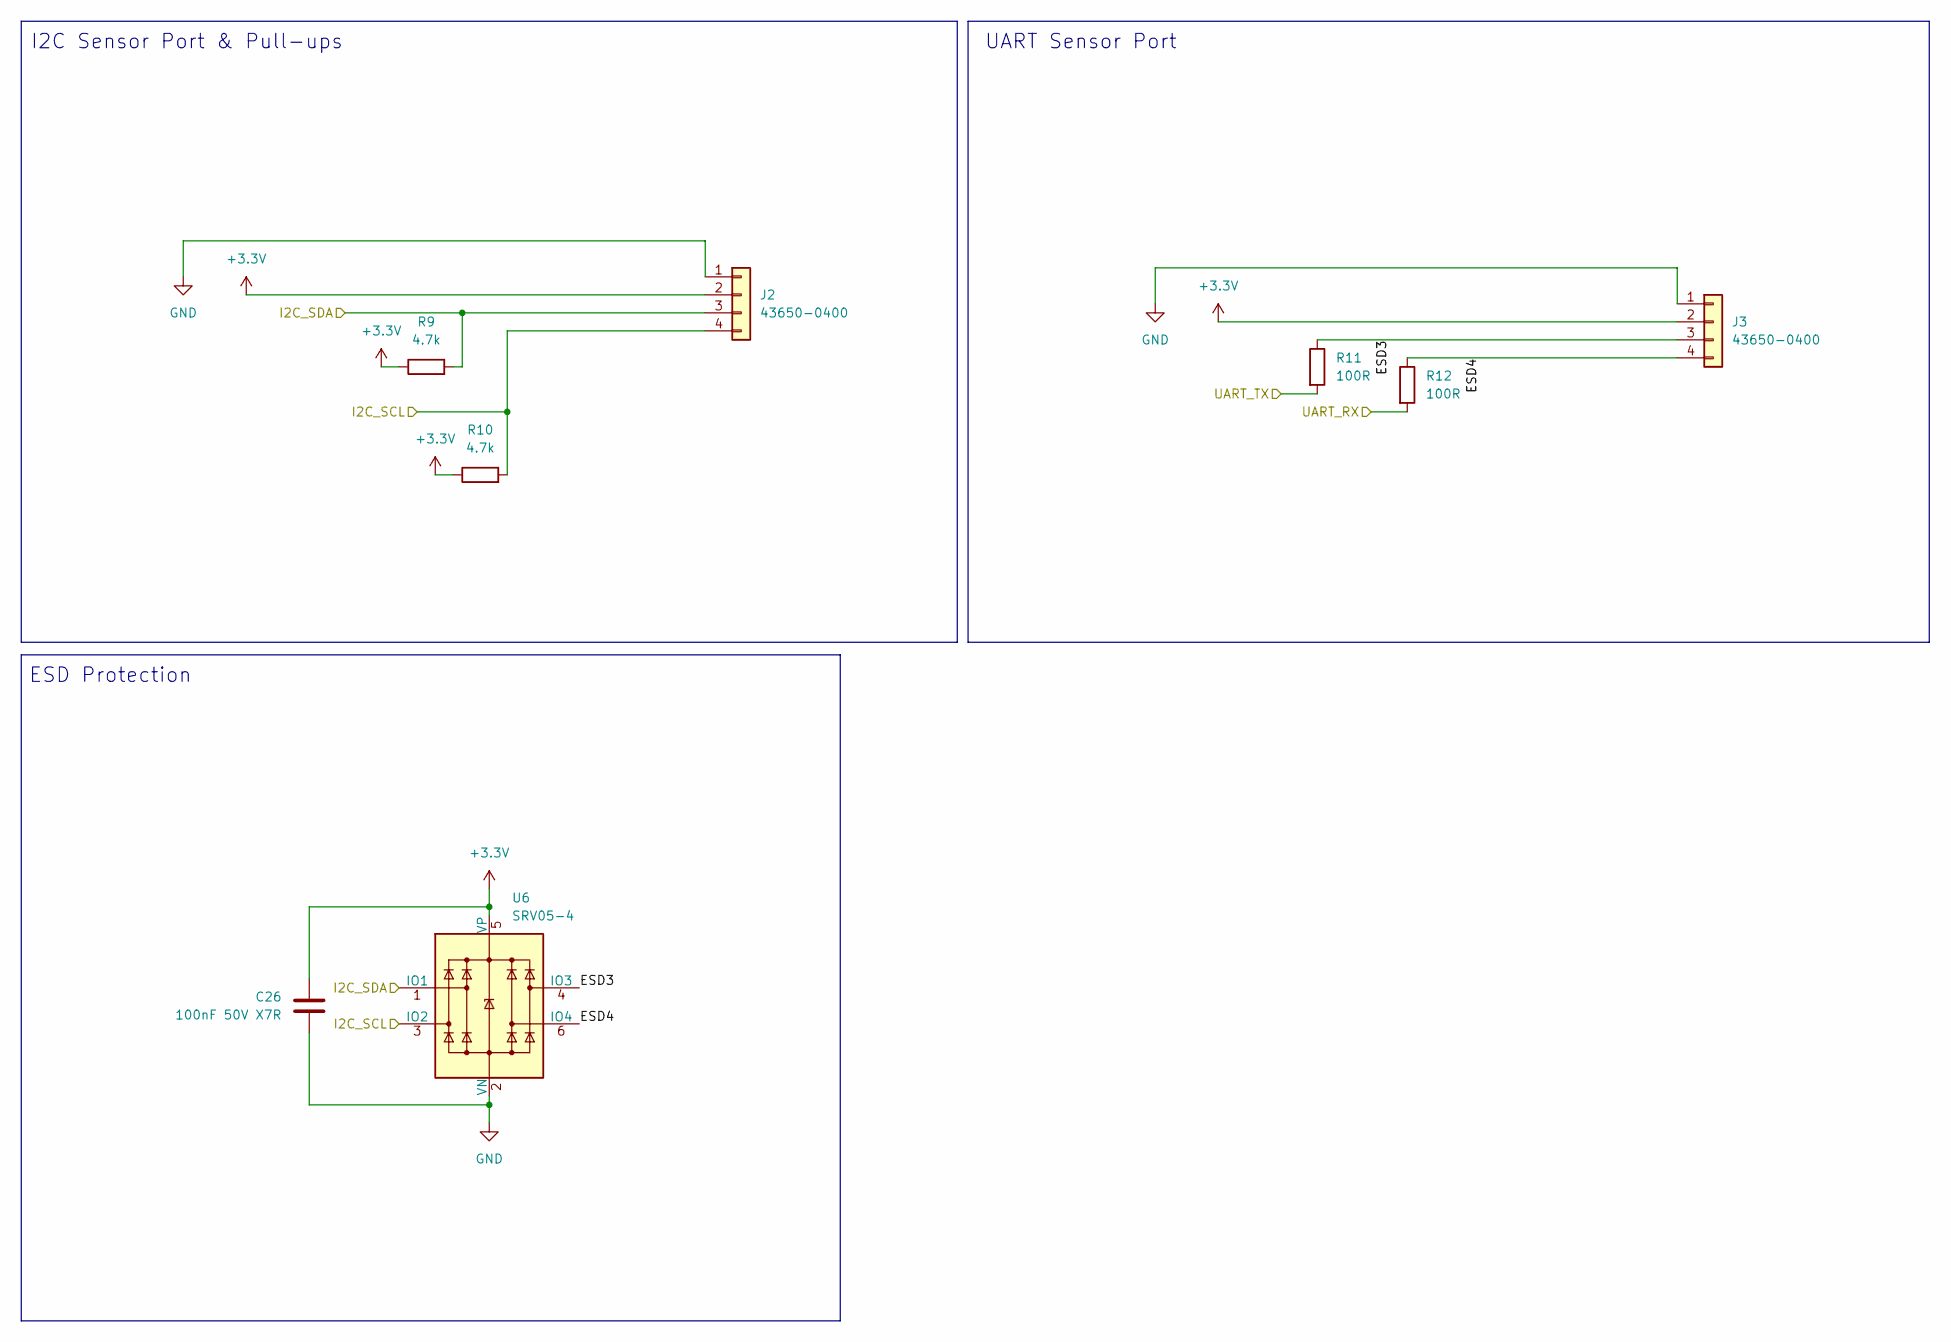
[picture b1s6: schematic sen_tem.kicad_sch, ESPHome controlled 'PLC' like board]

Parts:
C26: 100nF 50V X7R; C_0603_1608Metric_Pad1.08x0.95mm_HandSolder
J2, J3: 43650-0400; Molex_Micro-Fit_3.0_43650-0400_1x04_P3.00mm_Horizontal
R9, R10: 4.7k; R_0603_1608Metric_Pad0.98x0.95mm_HandSolder
R11, R12: 100R; R_0603_1608Metric_Pad0.98x0.95mm_HandSolder
U6: SRV05-4; SOT-23-6_Handsoldering

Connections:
+3.3V: C26.2, J2.2, J3.2, R9.1, R10.1, U6.5 (VP); also elsewhere on the board
/MCU Core/I2C_SCL: J2.4, R10.2, U6.3 (IO2); also elsewhere on the board
/MCU Core/I2C_SDA: J2.3, R9.2, U6.1 (IO1); also elsewhere on the board
/MCU Core/UART_RX: R12.2; also elsewhere on the board
/MCU Core/UART_TX: R11.2; also elsewhere on the board
/Sensors Telemetry/ESD3: J3.3, R11.1, U6.4 (IO3)
/Sensors Telemetry/ESD4: J3.4, R12.1, U6.6 (IO4)
GND: C26.1, J2.1, J3.1, U6.2 (VN); also elsewhere on the board

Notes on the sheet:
ESD Protection
I2C Sensor Port & Pull-ups
UART Sensor Port

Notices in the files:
README.md:
License: Firmware
